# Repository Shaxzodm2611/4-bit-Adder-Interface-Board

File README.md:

# 4-bit Adder Interface Board

> **AI-generated README**: This README was generated with AI from the repository contents and may contain mistakes or omissions. Please verify hardware details, part numbers, and wiring against the KiCad source files before using it as authoritative documentation.

## Overview

This repository contains KiCad design files for a custom PCB titled **4 Bit - Seven Seg Interface**. The project appears to be a discrete-logic interface board built around a 4-bit adder and related support circuitry, intended to drive or interface with a seven-segment display.

The repository description indicates it is:

> “A custom PCB designed to mimic the function of a CPU. Entirely made from discrete logic ICs.”

## What is in the repository

The project is organized as a KiCad hardware design with schematic sheets and board/layout files, including:

- **PCB layout**: `4 Bit - Seven Seg Interface.kicad_pcb`
- **KiCad project**: `4 Bit - Seven Seg Interface.kicad_pro`
- **Main schematic**: `4 Bit - Seven Seg Interface.kicad_sch`
- **Supporting schematics**:
  - `Adders.kicad_sch`
  - `Registers.kicad_sch`
  - `Decoder.kicad_sch`
  - `Hex.kicad_sch`
  - `A.kicad_sch`
  - `C&D.kicad_sch`
  - `G.kicad_sch`
  - `555Timer.kicad_sch`
  - `untitled.kicad_sch`
- **Footprint libraries**:
  - `Components.pretty/`
  - `15000LED.pretty/`
- **Backup files**:
  - `4 Bit - Seven Seg Interface-backups/`

## Project structure and inferred function

From the schematic names and symbols used in the design, the board likely includes:

- **4-bit adder stage** using a `CD74HC283M96` 4-bit binary adder
- **Register / storage logic** using flip-flops and DIP switch inputs
- **Decoder / inverter logic** for signal conditioning and display control
- **Seven-segment display interface** using an `LSHD-7503` display component
- **Clock/timing circuitry** using a `555Timer` schematic section
- **Discrete logic gates** such as AND, OR, and NOT devices from the SN74LVC and CD4000 families

## Notable components seen in the schematics

A few parts are visible in the schematic source:

- `CD74HC283M96` — 4-bit binary adder
- `SN74LVC1G08DBVR` — 2-input AND gate
- `SN74LVC1G11DBVR` — 3-input AND gate
- `SN74LVC1G32DCKR` — 2-input OR gate
- `SN74LVC1G14DCKR` — inverter / Schmitt trigger
- `SN74LVC1G175DCKR` — D flip-flop with async clear
- `CD4072BM96` — dual 4-input OR gate
- `LSHD-7503` — seven-segment display
- `CFS-0102TB` — DIP switch component
- `219-8MST` — switch component
- LEDs, resistors, and capacitors for support circuitry

## Likely purpose

Based on the file names and symbols, this board seems intended to:

- accept switch inputs
- store or route 4-bit values
- perform addition with a 4-bit adder
- decode or condition signals
- display results on a seven-segment display

## Getting started

To work with this repository:

1. Install a compatible version of **KiCad 8**.
2. Open `4 Bit - Seven Seg Interface.kicad_pro` in KiCad.
3. Inspect the schematic sheets and PCB layout.
4. Review footprints and part choices before fabrication.

## Manufacturing / fabrication notes

This repository appears to be a hardware design project, so you will likely need to:

- verify all footprints
- confirm net connectivity and board rules in KiCad
- generate Gerbers, drill files, and BOM from the project
- review backups and autosave files before committing to fabrication

## Caveats

Because this README was generated automatically:

- component roles may be inferred incorrectly
- sheet names may not perfectly describe their actual logic
- some file names may represent work-in-progress or unused sheets
- exact electrical behavior should be confirmed in KiCad

## License

No license file was found in the repository contents examined here. If you plan to reuse or distribute the design, check with the repository owner or add an explicit license.

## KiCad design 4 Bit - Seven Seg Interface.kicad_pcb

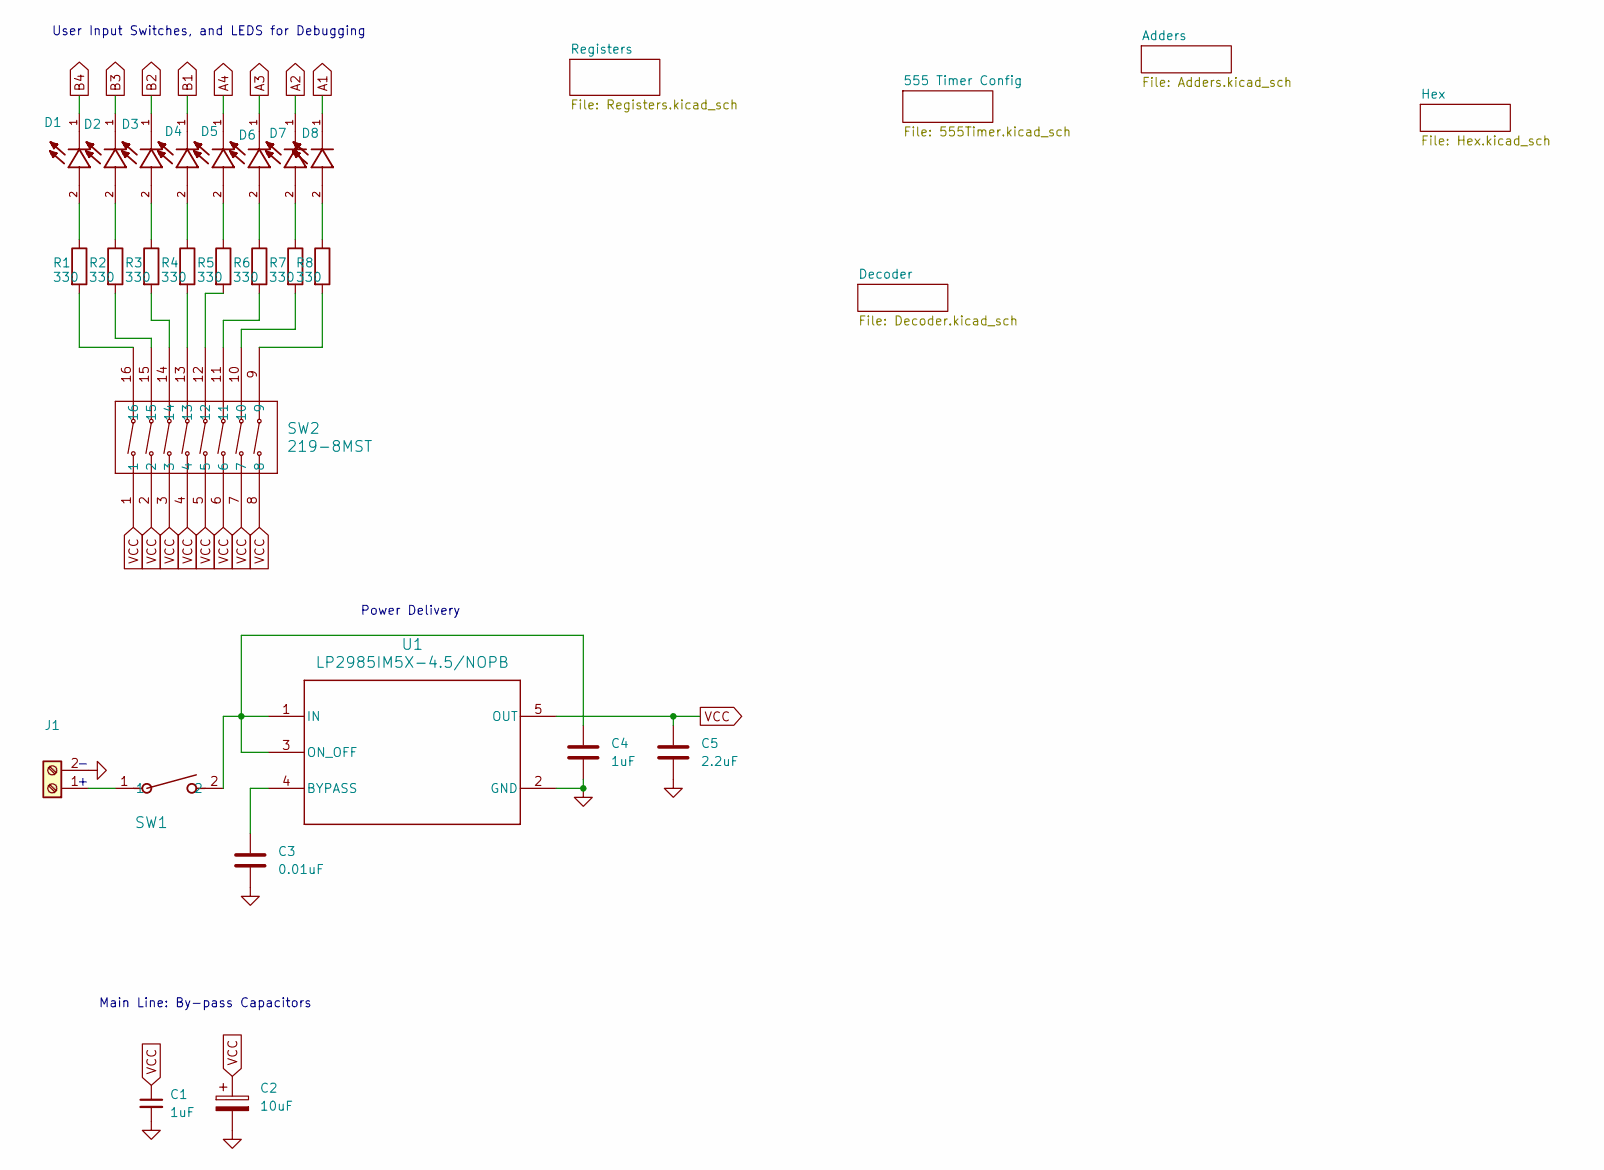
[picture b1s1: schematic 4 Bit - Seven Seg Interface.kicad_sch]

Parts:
C1, C4: 1uF; C_0603_1608Metric_Pad1.08x0.95mm_HandSolder
C2: 10uF; 10uF electrolytic Capacitor
C3: 0.01uF; C_0603_1608Metric_Pad1.08x0.95mm_HandSolder
C5: 2.2uF; C_0603_1608Metric_Pad1.08x0.95mm_HandSolder
D1, D2, D3, D4, D5, D6, D7, D8: 150060RS75000; LED_150060RS75000; PARTREV 2/26/2019
J1: Screw_Terminal_01x02; Screw-in Terminal
R1, R2, R3, R4, R5, R6, R7, R8: 330; R330-0805
SW1: CFS-0102TB; SW2_CFS-0102TB_NDC
SW2: 219-8MST; SO16_219-8_CTS
U1: LP2985IM5X-4.5/NOPB; DBV0005A_N (16v - 4.5 v VREG)com

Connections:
A1: D8.1; also elsewhere on the board
A2: D7.1; also elsewhere on the board
A3: D6.1; also elsewhere on the board
A4: D5.1; also elsewhere on the board
B1: D4.1; also elsewhere on the board
B2: D3.1; also elsewhere on the board
B3: D2.1; also elsewhere on the board
B4: D1.1; also elsewhere on the board
GND: C1.2, C2.2, C3.2, C4.2, C5.2, J1.2, U1.2 (GND); also elsewhere on the board
unnamed: D1.2, R1.1
unnamed: D2.2, R2.1
unnamed: D3.2, R3.1
unnamed: D4.2, R4.1
unnamed: D5.2, R5.1
unnamed: D6.2, R6.1
unnamed: D7.2, R7.1
unnamed: D8.2, R8.1
unnamed 29: J1.1, SW1.1; also elsewhere on the board
unnamed: R1.2, SW2.16
unnamed: R2.2, SW2.15
unnamed: R3.2, SW2.14
unnamed: R4.2, SW2.13
unnamed: R5.2, SW2.12
unnamed: R6.2, SW2.11
unnamed: R7.2, SW2.10
unnamed: R8.2, SW2.9
unnamed: C3.1, U1.4 (BYPASS)
unnamed 39: C4.1, SW1.2, U1.1 (IN), U1.3 (ON_OFF); also elsewhere on the board
VCC: C1.1, C2.1, C5.1, SW2.1, SW2.2, SW2.3, SW2.4, SW2.5, SW2.6, SW2.7, SW2.8, U1.5 (OUT); also elsewhere on the board

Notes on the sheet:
Power Delivery
Main Line: By-pass Capacitors
User Input Switches, and LEDS for Debugging

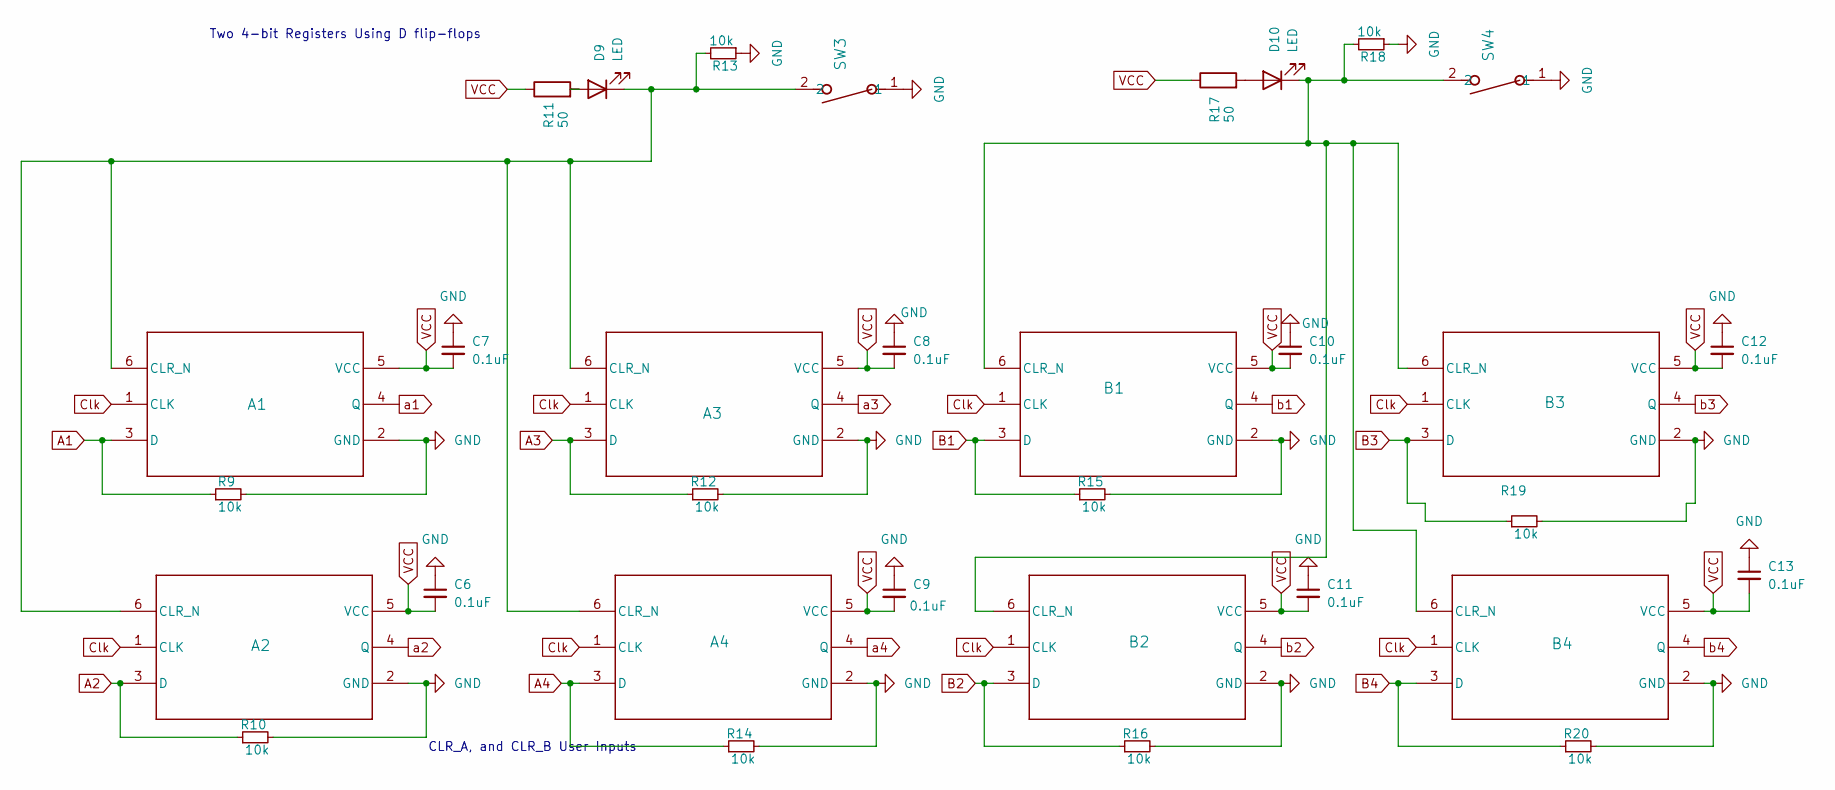
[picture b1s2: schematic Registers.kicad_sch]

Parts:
A1, A2, A3, A4: SN74LVC1G175DCKR; DCK0006A_N
B1, B2, B3, B4: SN74LVC1G175DCKR; DCK0006A_N
C6, C7, C8, C9, C10, C11, C12, C13: 0.1uF; 0603-0.1uF
D9, D10: LED; GLED0805
R9, R10, R12, R13, R14, R15, R16, R18, R19, R20: 10k; R805-10k
R11, R17: 50; 0603R-50ohms
SW3, SW4: CFS-0102TB; SW2_CFS-0102TB_NDC

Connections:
A1: A1.3 (D), R9.1; also elsewhere on the board
A2: A2.3 (D), R10.1; also elsewhere on the board
A3: A3.3 (D), R12.1; also elsewhere on the board
A4: A4.3 (D), R14.1; also elsewhere on the board
B1: B1.3 (D), R15.1; also elsewhere on the board
B2: B2.3 (D), R16.1; also elsewhere on the board
B3: B3.3 (D), R19.1; also elsewhere on the board
B4: B4.3 (D), R20.1; also elsewhere on the board
Clk: A1.1 (CLK), A2.1 (CLK), A3.1 (CLK), A4.1 (CLK), B1.1 (CLK), B2.1 (CLK), B3.1 (CLK), B4.1 (CLK); also elsewhere on the board
GND: A1.2 (GND), A2.2 (GND), A3.2 (GND), A4.2 (GND), B1.2 (GND), B2.2 (GND), B3.2 (GND), B4.2 (GND), C6.1, C7.1, C8.1, C9.1, C10.1, C11.1, C12.1, C13.1, R9.2, R10.2, R12.2, R13.1, R14.2, R15.2, R16.2, R18.1, R19.2, R20.2, SW3.1, SW4.1; also elsewhere on the board
unnamed: A1.6 (CLR_N), A2.6 (CLR_N), A3.6 (CLR_N), A4.6 (CLR_N), D9.1 (K), R13.2, SW3.2
unnamed: B1.6 (CLR_N), B2.6 (CLR_N), B3.6 (CLR_N), B4.6 (CLR_N), D10.1 (K), R18.2, SW4.2
unnamed: D9.2 (A), R11.2
unnamed: D10.2 (A), R17.2
VCC: A1.5 (VCC), A2.5 (VCC), A3.5 (VCC), A4.5 (VCC), B1.5 (VCC), B2.5 (VCC), B3.5 (VCC), B4.5 (VCC), C6.2, C7.2, C8.2, C9.2, C10.2, C11.2, C12.2, C13.2, R11.1, R17.1; also elsewhere on the board
a1: A1.4 (Q); also elsewhere on the board
a2: A2.4 (Q); also elsewhere on the board
a3: A3.4 (Q); also elsewhere on the board
a4: A4.4 (Q); also elsewhere on the board
b1: B1.4 (Q); also elsewhere on the board
b2: B2.4 (Q); also elsewhere on the board
b3: B3.4 (Q); also elsewhere on the board
b4: B4.4 (Q); also elsewhere on the board

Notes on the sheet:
CLR_A, and CLR_B User Inputs
Two 4-bit Registers Using D flip-flops

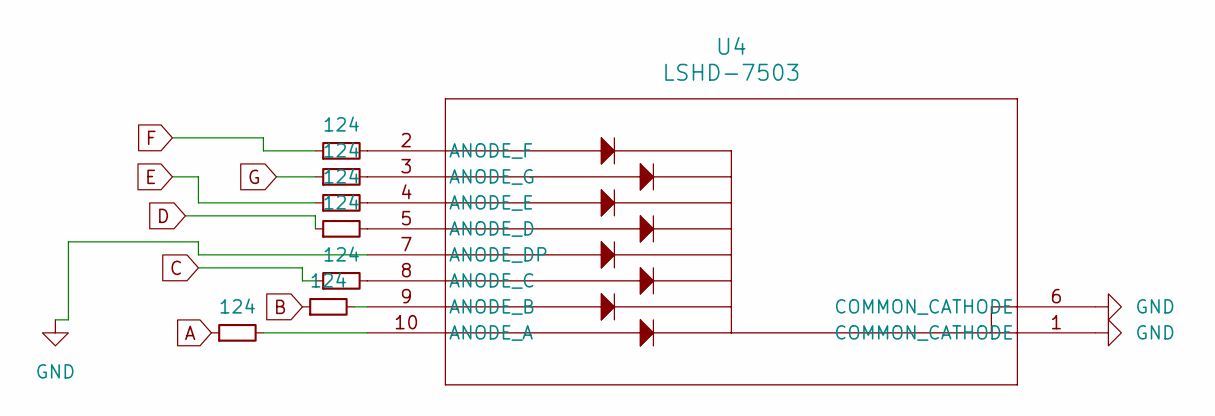
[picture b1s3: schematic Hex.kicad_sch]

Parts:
R23, R24, R25, R26, R27, R28, R29: 124; R_0603_1608Metric
U4: LSHD-7503; DIP10_LSHD-7503_LTO

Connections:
A: R23.1; also elsewhere on the board
B: R24.1; also elsewhere on the board
C: R29.1; also elsewhere on the board
D: R28.1; also elsewhere on the board
E: R27.1; also elsewhere on the board
F: R25.1; also elsewhere on the board
G: R26.1; also elsewhere on the board
GND: U4.1 (COMMON_CATHODE), U4.6 (COMMON_CATHODE), U4.7 (ANODE_DP); also elsewhere on the board
unnamed: R23.2, U4.10 (ANODE_A)
unnamed: R24.2, U4.9 (ANODE_B)
unnamed: R29.2, U4.8 (ANODE_C)
unnamed: R28.2, U4.5 (ANODE_D)
unnamed: R27.2, U4.4 (ANODE_E)
unnamed: R25.2, U4.2 (ANODE_F)
unnamed: R26.2, U4.3 (ANODE_G)

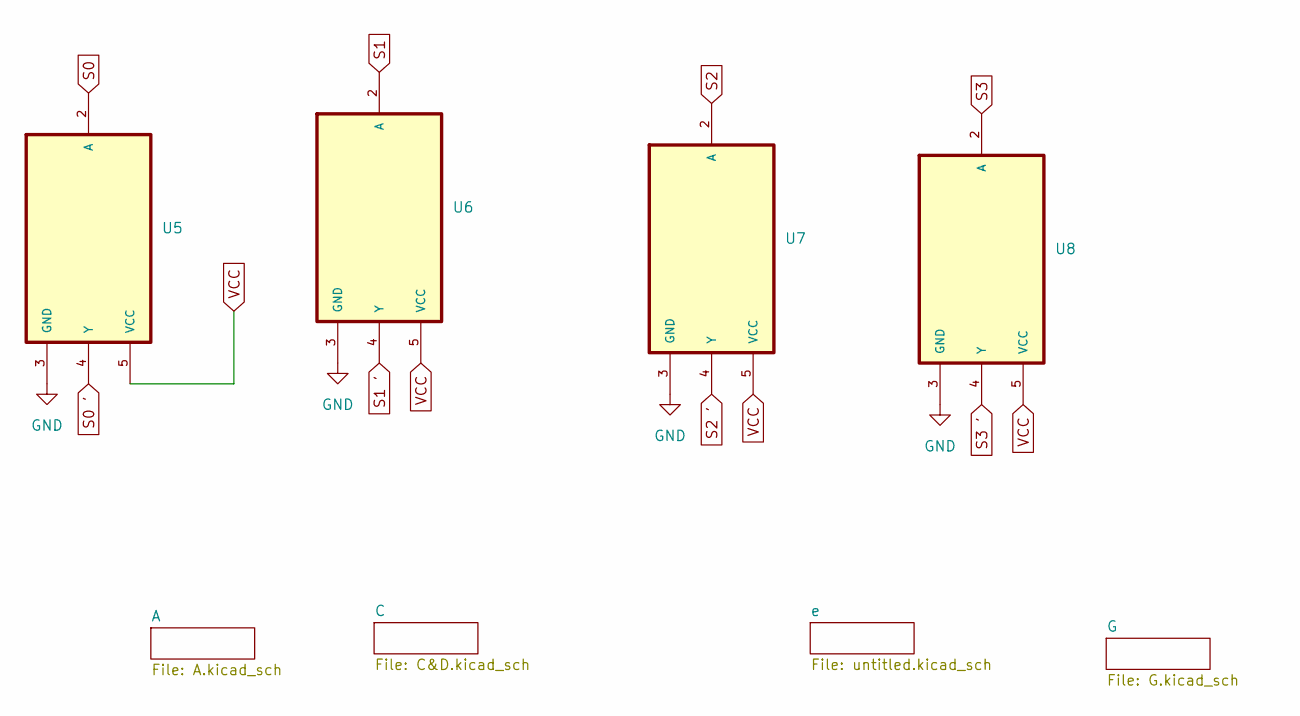
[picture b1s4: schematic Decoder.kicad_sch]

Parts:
U5, U6, U7, U8: SN74LVC1G14DCKR; 1INPUT_NOTGATE

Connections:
GND: U5.3 (GND), U6.3 (GND), U7.3 (GND), U8.3 (GND); also elsewhere on the board
S0: U5.2 (A); also elsewhere on the board
S0 ': U5.4 (Y); also elsewhere on the board
S1: U6.2 (A); also elsewhere on the board
S1 ': U6.4 (Y); also elsewhere on the board
S2: U7.2 (A); also elsewhere on the board
S2 ': U7.4 (Y); also elsewhere on the board
S3: U8.2 (A); also elsewhere on the board
S3 ': U8.4 (Y); also elsewhere on the board
VCC: U5.5 (VCC), U6.5 (VCC), U7.5 (VCC), U8.5 (VCC); also elsewhere on the board

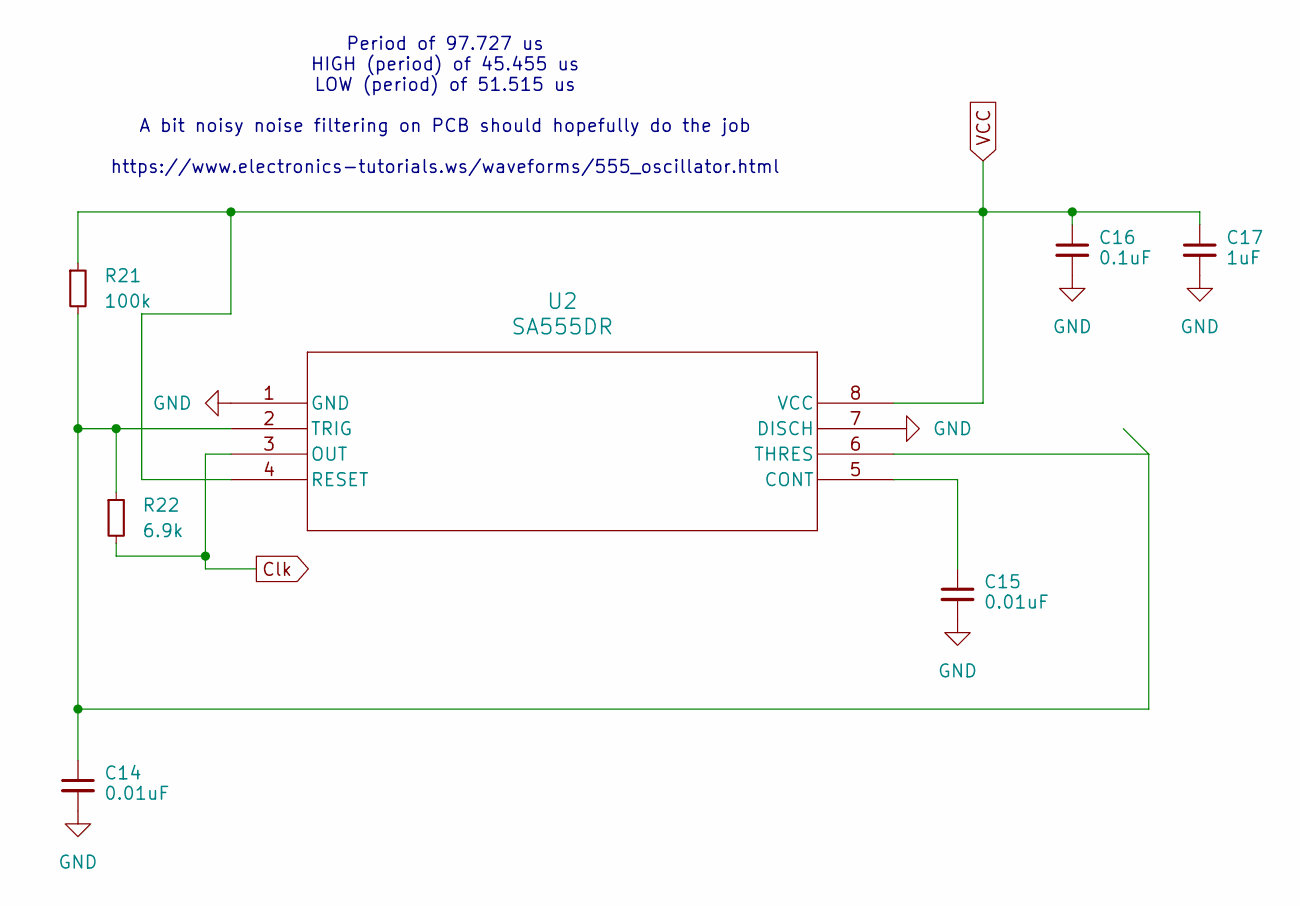
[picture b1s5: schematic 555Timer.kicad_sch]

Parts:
C14, C15: 0.01uF; C_0603_1608Metric_Pad1.08x0.95mm_HandSolder
C16: 0.1uF; C_0603_1608Metric_Pad1.08x0.95mm_HandSolder
C17: 1uF; C_0603_1608Metric_Pad1.08x0.95mm_HandSolder
R21: 100k; R_0603_1608Metric
R22: 6.9k; R_0603_1608Metric
U2: SA555DR; D8

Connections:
Clk: R22.2, U2.3 (OUT); also elsewhere on the board
GND: C14.2, C15.2, C16.2, C17.2, U2.1 (GND), U2.7 (DISCH); also elsewhere on the board
unnamed: C15.1, U2.5 (CONT)
unnamed: C14.1, R21.2, R22.1, U2.2 (TRIG), U2.6 (THRES)
VCC: C16.1, C17.1, R21.1, U2.4 (RESET), U2.8 (VCC); also elsewhere on the board

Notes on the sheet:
Period of 97.727 us HIGH (period) of 45.455 us LOW (period) of 51.515 us A bit noisy noise filtering on PCB should hopefully do the job https://www.electronics-tutorials.ws/waveforms/555_oscillator.html

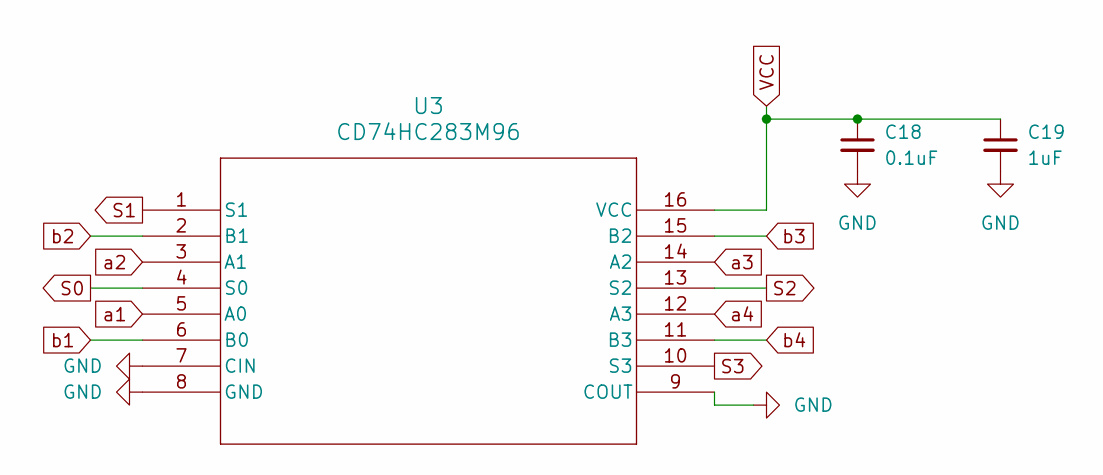
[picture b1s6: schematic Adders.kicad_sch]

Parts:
C18: 0.1uF; C_0603_1608Metric
C19: 1uF; C_0603_1608Metric
U3: CD74HC283M96; CD74HC283M96 (4-bit Binary Adder)

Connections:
GND: C18.2, C19.2, U3.7 (CIN), U3.8 (GND), U3.9 (COUT); also elsewhere on the board
S0: U3.4 (S0); also elsewhere on the board
S1: U3.1 (S1); also elsewhere on the board
S2: U3.13 (S2); also elsewhere on the board
S3: U3.10 (S3); also elsewhere on the board
VCC: C18.1, C19.1, U3.16 (VCC); also elsewhere on the board
a1: U3.5 (A0); also elsewhere on the board
a2: U3.3 (A1); also elsewhere on the board
a3: U3.14 (A2); also elsewhere on the board
a4: U3.12 (A3); also elsewhere on the board
b1: U3.6 (B0); also elsewhere on the board
b2: U3.2 (B1); also elsewhere on the board
b3: U3.15 (B2); also elsewhere on the board
b4: U3.11 (B3); also elsewhere on the board

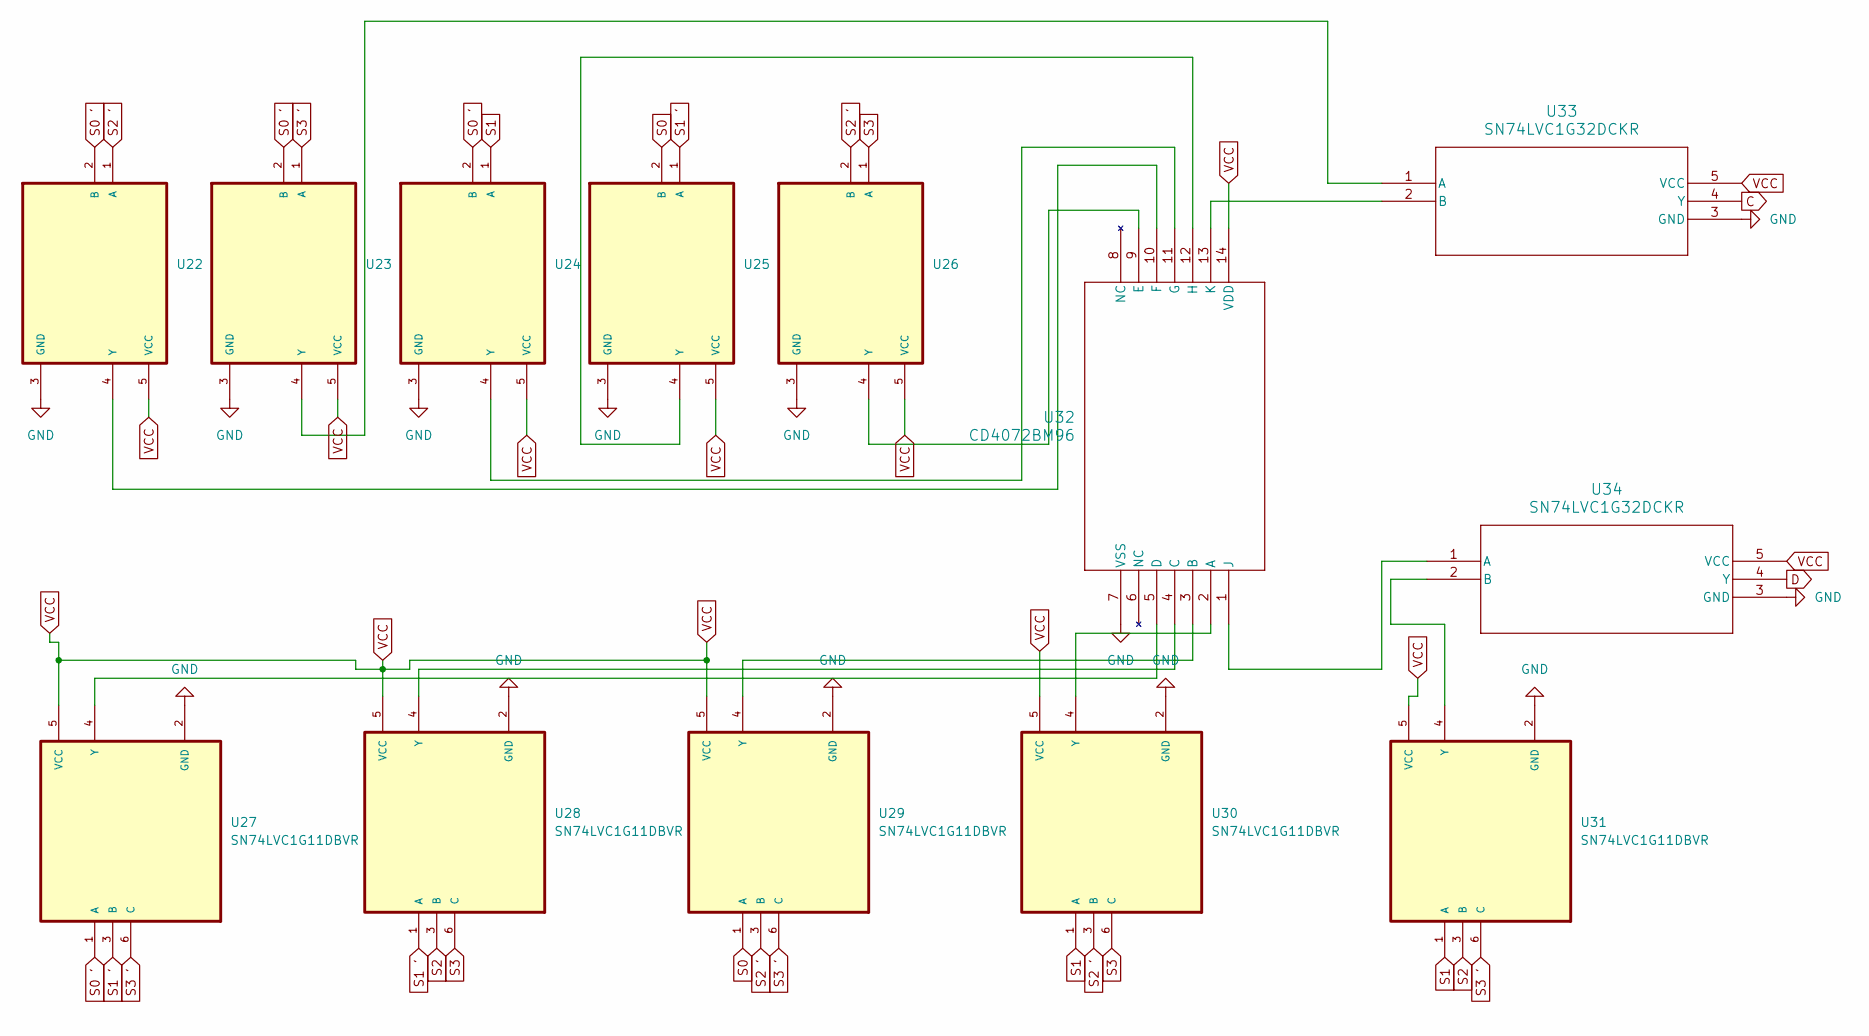
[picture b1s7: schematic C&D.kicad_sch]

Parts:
U22, U23, U24, U25, U26: SN74LVC1G08DBVR; SOT95P280X145-5N
U27, U28, U29, U30, U31: SN74LVC1G11DBVR; 3-INPUT AND
U32: CD4072BM96; 4-INPUT 2-CHN OR
U33, U34: SN74LVC1G32DCKR; 2-INPUT OR

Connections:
C: U33.4 (Y); also elsewhere on the board
D: U34.4 (Y); also elsewhere on the board
GND: U22.3 (GND), U23.3 (GND), U24.3 (GND), U25.3 (GND), U26.3 (GND), U27.2 (GND), U28.2 (GND), U29.2 (GND), U30.2 (GND), U31.2 (GND), U32.7 (VSS), U33.3 (GND), U34.3 (GND); also elsewhere on the board
unnamed: U22.4 (Y), U32.10 (F)
unnamed: U23.4 (Y), U33.1 (A)
unnamed: U24.4 (Y), U32.11 (G)
unnamed: U25.4 (Y), U32.12 (H)
unnamed: U26.4 (Y), U32.9 (E)
unnamed: U27.4 (Y), U32.5 (D)
unnamed: U28.4 (Y), U32.4 (C)
unnamed: U29.4 (Y), U32.3 (B)
unnamed: U30.4 (Y), U32.2 (A)
unnamed: U31.4 (Y), U34.2 (B)
unnamed: U32.1 (J), U34.1 (A)
unnamed: U32.13 (K), U33.2 (B)
S0: U25.2 (B), U29.1 (A); also elsewhere on the board
S0 ': U22.2 (B), U23.2 (B), U24.2 (B), U27.1 (A); also elsewhere on the board
S1: U24.1 (A), U30.1 (A), U31.1 (A); also elsewhere on the board
S1 ': U25.1 (A), U27.3 (B), U28.1 (A); also elsewhere on the board
S2: U28.3 (B), U31.3 (B); also elsewhere on the board
S2 ': U22.1 (A), U26.2 (B), U29.3 (B), U30.3 (B); also elsewhere on the board
S3: U26.1 (A), U28.6 (C), U30.6 (C); also elsewhere on the board
S3 ': U23.1 (A), U27.6 (C), U29.6 (C), U31.6 (C); also elsewhere on the board
VCC: U22.5 (VCC), U23.5 (VCC), U24.5 (VCC), U25.5 (VCC), U26.5 (VCC), U27.5 (VCC), U28.5 (VCC), U29.5 (VCC), U30.5 (VCC), U31.5 (VCC), U32.14 (VDD), U33.5 (VCC), U34.5 (VCC); also elsewhere on the board

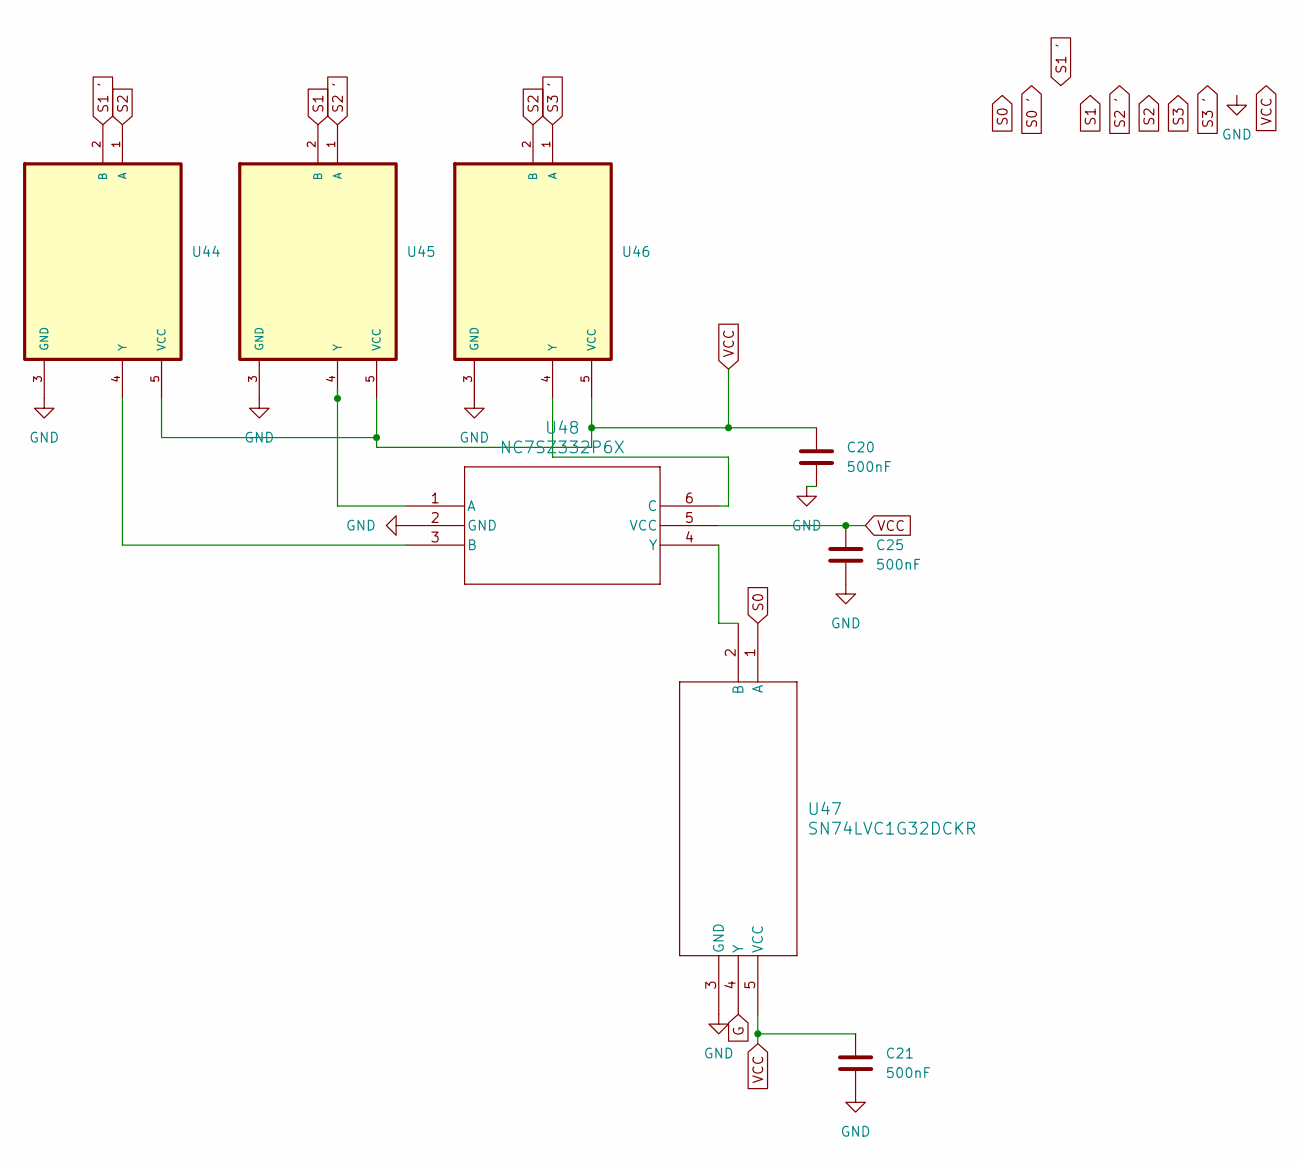
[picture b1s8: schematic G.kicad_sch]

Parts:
C20, C21, C25: 500nF; C_0603_1608Metric_Pad1.08x0.95mm_HandSolder
U44, U45, U46: SN74LVC1G08DBVR; SOT95P280X145-5N
U47: SN74LVC1G32DCKR; 2-INPUT OR
U48: NC7SZ332P6X; 3-INPUT OR

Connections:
G: U47.4 (Y); also elsewhere on the board
GND: C20.1, C21.1, C25.1, U44.3 (GND), U45.3 (GND), U46.3 (GND), U47.3 (GND), U48.2 (GND); also elsewhere on the board
unnamed: U44.4 (Y), U48.3 (B)
unnamed: U45.4 (Y), U48.1 (A)
unnamed: U46.4 (Y), U48.6 (C)
unnamed: U47.2 (B), U48.4 (Y)
S0: U47.1 (A); also elsewhere on the board
S1: U45.2 (B); also elsewhere on the board
S1 ': U44.2 (B); also elsewhere on the board
S2: U44.1 (A), U46.2 (B); also elsewhere on the board
S2 ': U45.1 (A); also elsewhere on the board
S3 ': U46.1 (A); also elsewhere on the board
VCC: C20.2, C21.2, C25.2, U44.5 (VCC), U45.5 (VCC), U46.5 (VCC), U47.5 (VCC), U48.5 (VCC); also elsewhere on the board

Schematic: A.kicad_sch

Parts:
U9, U10, U16, U17, U18, U19: SN74LVC1G11DBVR; 3-INPUT AND
U11, U12, U13, U20: SN74LVC1G08DBVR; SOT95P280X145-5N
U14: CD4072BM96; 4-INPUT 2-CHN OR
U15, U21: SN74LVC1G32DCKR; 2-INPUT OR

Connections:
A: U15.4 (Y); also elsewhere on the board
B: U21.4 (Y); also elsewhere on the board
GND: U9.2 (GND), U10.2 (GND), U11.3 (GND), U12.3 (GND), U13.3 (GND), U14.7 (VSS), U15.3 (GND), U16.2 (GND), U17.2 (GND), U18.2 (GND), U19.2 (GND), U20.3 (GND), U21.3 (GND); also elsewhere on the board
unnamed: U10.4 (Y), U14.3 (B)
unnamed: U11.4 (Y), U14.2 (A)
unnamed: U12.4 (Y), U14.4 (C)
unnamed: U13.4 (Y), U15.1 (A)
unnamed: U9.4 (Y), U14.5 (D)
unnamed: U14.9 (E), U17.4 (Y)
unnamed: U14.10 (F), U19.4 (Y)
unnamed: U14.11 (G), U18.4 (Y)
unnamed: U14.12 (H), U16.4 (Y)
unnamed: U14.1 (J), U15.2 (B)
unnamed: U14.13 (K), U21.1 (A)
unnamed: U20.4 (Y), U21.2 (B)
S0: U10.1 (A), U18.1 (A), U19.3 (B); also elsewhere on the board
S0 ': U9.6 (C), U11.2 (B), U16.1 (A), U17.1 (A); also elsewhere on the board
S1: U9.3 (B), U13.1 (A); also elsewhere on the board
S1 ': U10.3 (B), U12.2 (B), U20.1 (A); also elsewhere on the board
S2: U11.1 (A), U13.2 (B), U17.3 (B), U19.6 (C); also elsewhere on the board
S2 ': U10.6 (C), U16.3 (B), U18.3 (B); also elsewhere on the board
S3: U9.1 (A), U17.6 (C), U18.6 (C); also elsewhere on the board
S3 ': U12.1 (A), U16.6 (C), U19.1 (A), U20.2 (B); also elsewhere on the board
VCC: U9.5 (VCC), U10.5 (VCC), U11.5 (VCC), U12.5 (VCC), U13.5 (VCC), U14.14 (VDD), U15.5 (VCC), U16.5 (VCC), U17.5 (VCC), U18.5 (VCC), U19.5 (VCC), U20.5 (VCC), U21.5 (VCC); also elsewhere on the board

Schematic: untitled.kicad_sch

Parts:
C22, C23, C24: 500nF; C_0603_1608Metric
U35, U36, U42: SN74LVC1G08DBVR; SOT95P280X145-5N
U37, U38, U39, U40, U41: SN74LVC1G11DBVR; 3-INPUT AND
U43: CD4072BM96; 4-INPUT 2-CHN OR

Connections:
E: U43.1 (J); also elsewhere on the board
F: U43.13 (K); also elsewhere on the board
GND: C22.2, C23.2, C24.2, U35.3 (GND), U36.3 (GND), U37.2 (GND), U38.2 (GND), U39.2 (GND), U40.2 (GND), U41.2 (GND), U42.3 (GND), U43.7 (VSS); also elsewhere on the board
unnamed: U35.4 (Y), U43.2 (A)
unnamed: U36.4 (Y), U43.3 (B)
unnamed: U37.4 (Y), U43.4 (C)
unnamed: U38.4 (Y), U43.5 (D)
unnamed: U39.4 (Y), U43.12 (H)
unnamed: U40.4 (Y), U43.11 (G)
unnamed: U41.4 (Y), U43.10 (F)
unnamed: U42.4 (Y), U43.9 (E)
S0: U37.3 (B), U38.6 (C), U42.1 (A); also elsewhere on the board
S0 ': U39.1 (A), U40.1 (A); also elsewhere on the board
S1: U38.1 (A), U40.6 (C), U41.1 (A); also elsewhere on the board
S1 ': U35.2 (B), U37.6 (C), U42.2 (B); also elsewhere on the board
S2: U36.2 (B), U37.1 (A), U41.3 (B); also elsewhere on the board
S2 ': U38.3 (B), U39.3 (B), U40.3 (B); also elsewhere on the board
S3 ': U35.1 (A), U36.1 (A), U39.6 (C), U41.6 (C); also elsewhere on the board
VCC: C22.1, C23.1, C24.1, U35.5 (VCC), U36.5 (VCC), U37.5 (VCC), U38.5 (VCC), U39.5 (VCC), U40.5 (VCC), U41.5 (VCC), U42.5 (VCC), U43.14 (VDD); also elsewhere on the board

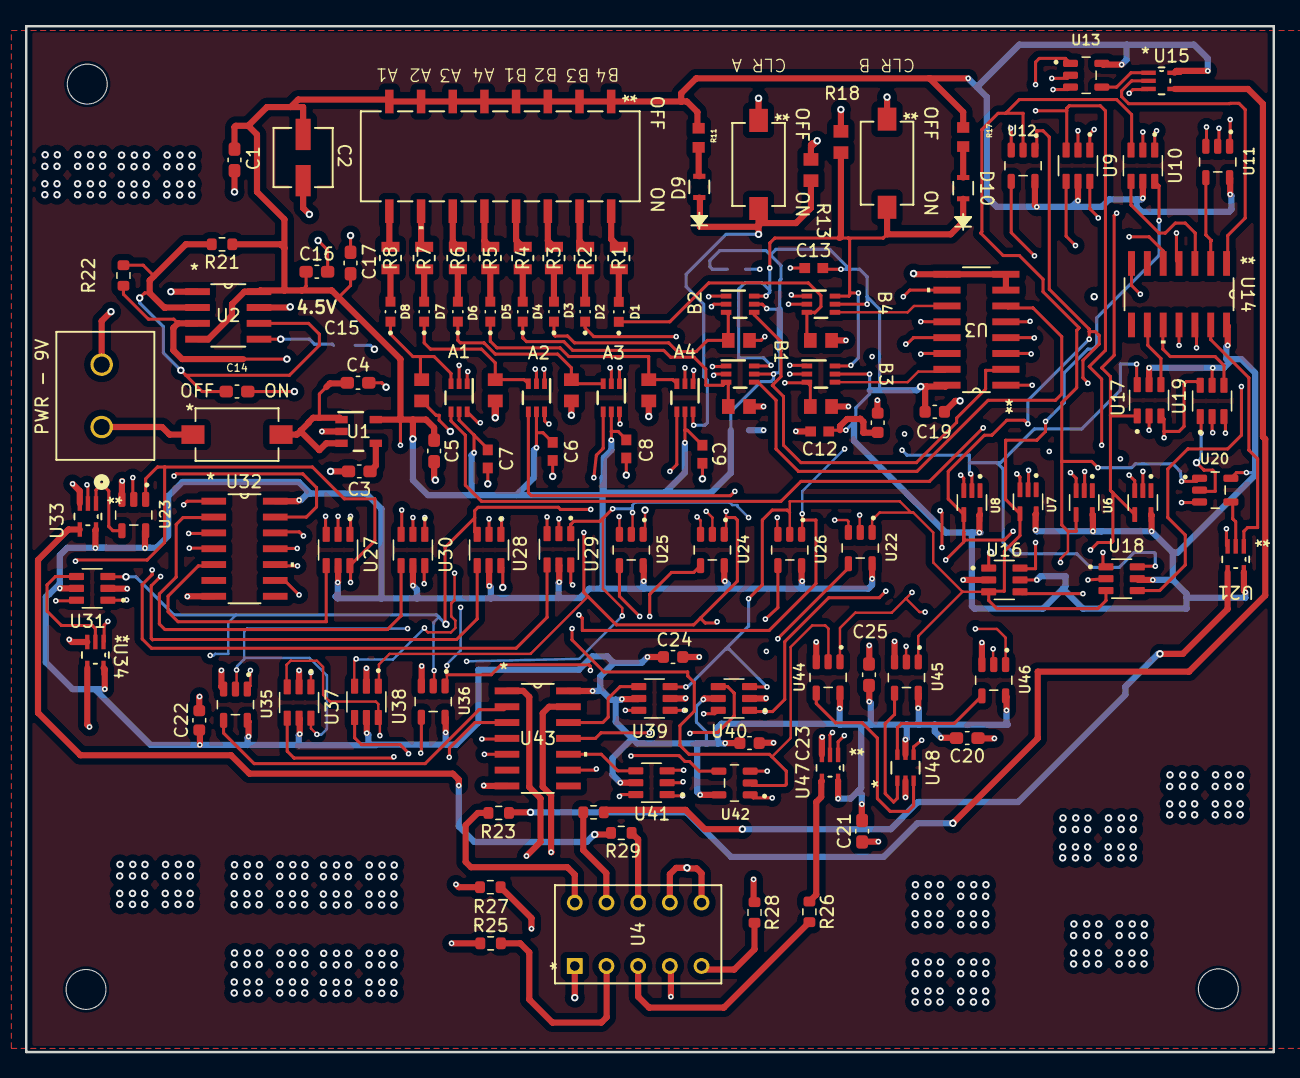
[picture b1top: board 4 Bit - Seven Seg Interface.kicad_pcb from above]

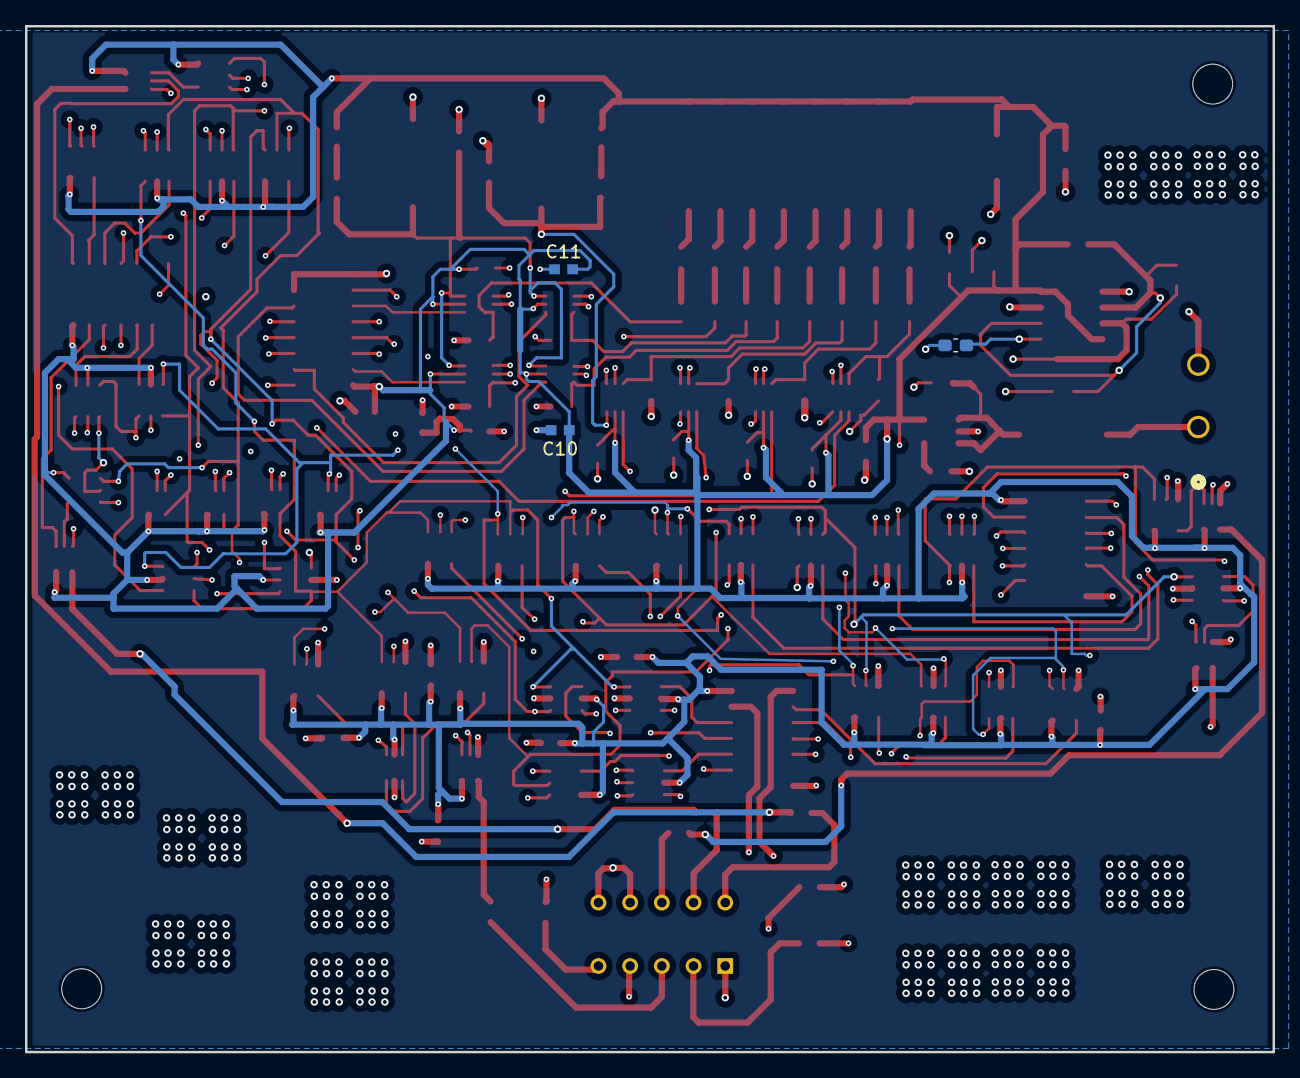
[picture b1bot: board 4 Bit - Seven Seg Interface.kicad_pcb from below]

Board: 4 copper layers, 100.0 x 82.2 mm, 125 parts (3 on the bottom side), 102 nets.

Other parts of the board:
PWR - 9V: CFS-0102TB; SW2_CFS-0102TB_NDC

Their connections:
unnamed 29: PWR - 9V.1; also elsewhere on the board
unnamed 39: PWR - 9V.2; also elsewhere on the board

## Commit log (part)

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2024-09-08 Add files via upload
    The raw ki-cad files for this project. As a note, this project currently does not function as intended, in the future, I intend to add a ADC so that the registers are able to read analog values. Furt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
